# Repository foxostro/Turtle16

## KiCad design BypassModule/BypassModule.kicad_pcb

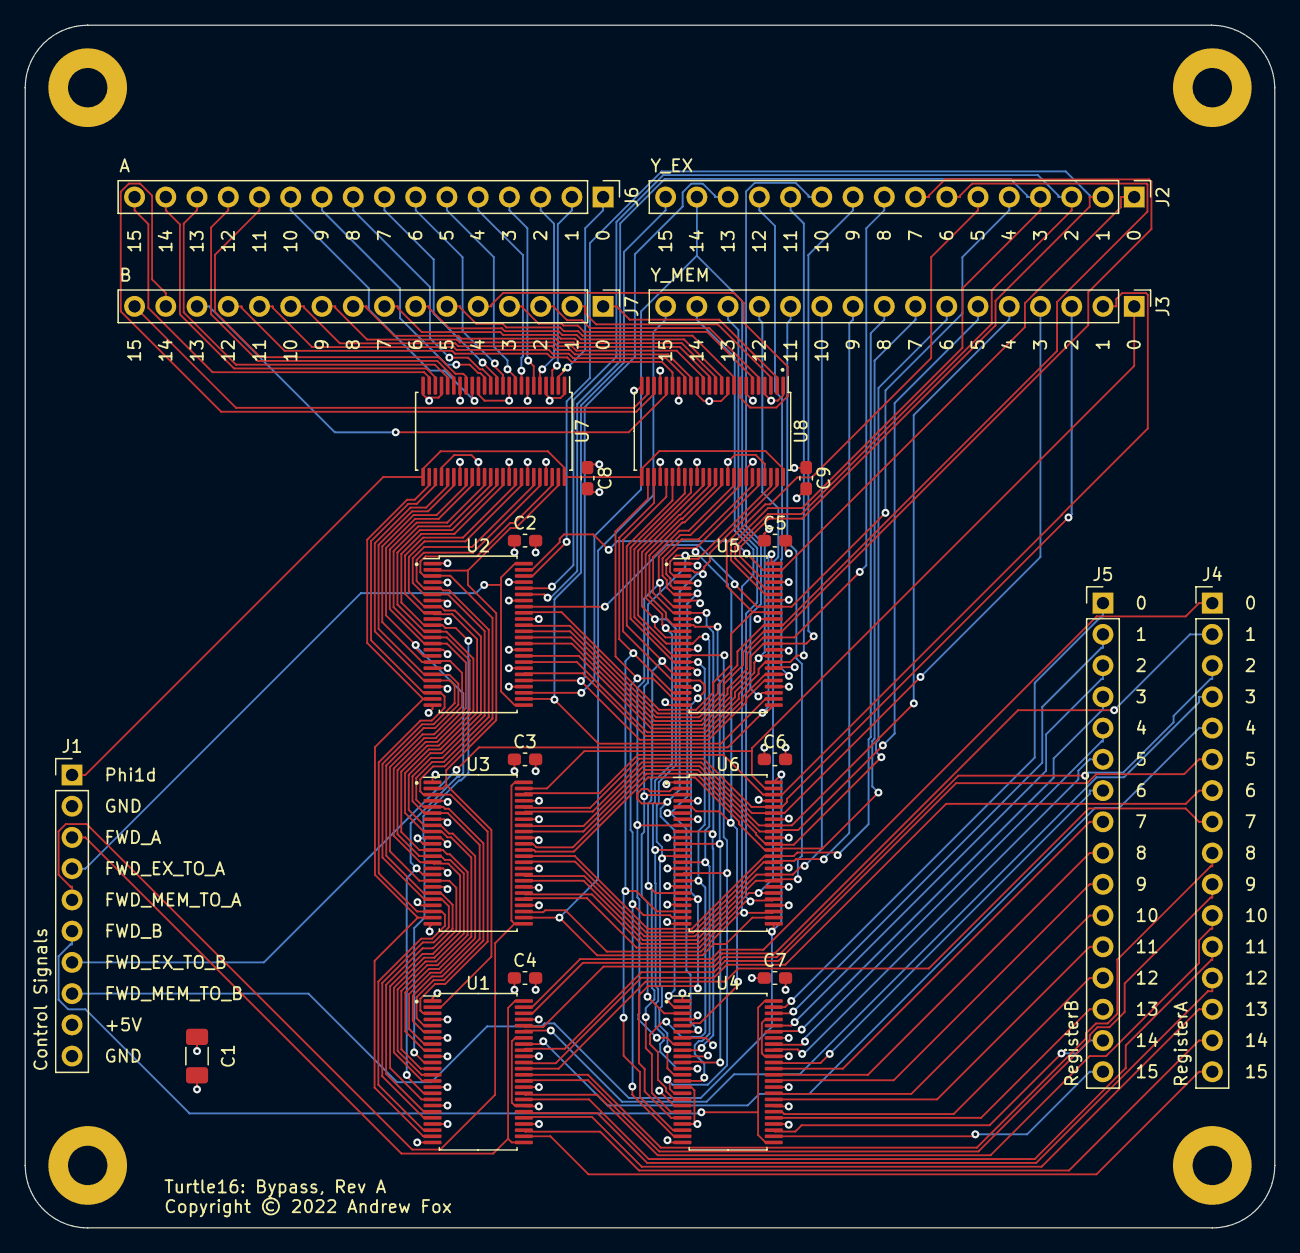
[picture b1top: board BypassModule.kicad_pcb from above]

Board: 4 copper layers, 101.6 x 97.8 mm, 28 parts (0 on the bottom side), 137 nets.

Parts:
C1: 100µF; C_1206_3216Metric_Pad1.33x1.80mm_HandSolder
C2, C3, C4, C5, C6, C7, C8, C9: 100nF; C_0603_1608Metric_Pad1.08x0.95mm_HandSolder
H1, H2, H3, H4: MountingHole_Pad; MountingHole_3.2mm_M3_Pad
J1: Control Signals; PinHeader_1x10_P2.54mm_Vertical
J2: Y_EX; PinHeader_1x16_P2.54mm_Vertical
J3: Y_MEM; PinHeader_1x16_P2.54mm_Vertical
J4: RegisterA; PinHeader_1x16_P2.54mm_Vertical
J5: RegisterB; PinHeader_1x16_P2.54mm_Vertical
J6: A; PinHeader_1x16_P2.54mm_Vertical
J7: B; PinHeader_1x16_P2.54mm_Vertical
U1, U2, U3, U4, U5, U6: 74AHCT16245; TSSOP-48_6.1x12.5mm_P0.5mm
U7, U8: 74ABT16374; TSSOP-48_6.1x12.5mm_P0.5mm

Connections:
/Bypass Prototype Inputs/FWD_A: J1.3, U1.25 (2~OE), U1.48 (1~OE)
/Bypass Prototype Inputs/FWD_B: J1.6, U4.25 (2~OE), U4.48 (1~OE)
/Bypass Prototype Inputs/FWD_EX_TO_A: J1.4, U2.25 (2~OE), U2.48 (1~OE)
/Bypass Prototype Inputs/FWD_EX_TO_B: J1.7, U5.25 (2~OE), U5.48 (1~OE)
/Bypass Prototype Inputs/FWD_MEM_TO_A: J1.5, U3.25 (2~OE), U3.48 (1~OE)
/Bypass Prototype Inputs/FWD_MEM_TO_B: J1.8, U6.25 (2~OE), U6.48 (1~OE)
/Bypass Prototype Inputs/Phi1d: J1.1, U7.25 (2CLK), U7.48 (1CLK), U8.25 (2CLK), U8.48 (1CLK)
/Bypass Prototype Inputs/RegisterA0: J4.1, U1.47 (1A1)
/Bypass Prototype Inputs/RegisterA1: J4.2, U1.46 (1A2)
/Bypass Prototype Inputs/RegisterA2: J4.3, U1.44 (1A3)
/Bypass Prototype Inputs/RegisterA3: J4.4, U1.43 (1A4)
/Bypass Prototype Inputs/RegisterA4: J4.5, U1.41 (1A5)
/Bypass Prototype Inputs/RegisterA5: J4.6, U1.40 (1A6)
/Bypass Prototype Inputs/RegisterA6: J4.7, U1.38 (1A7)
/Bypass Prototype Inputs/RegisterA7: J4.8, U1.37 (1A8)
/Bypass Prototype Inputs/RegisterA8: J4.9, U1.36 (2A1)
/Bypass Prototype Inputs/RegisterA9: J4.10, U1.35 (2A2)
/Bypass Prototype Inputs/RegisterA10: J4.11, U1.33 (2A3)
/Bypass Prototype Inputs/RegisterA11: J4.12, U1.32 (2A4)
/Bypass Prototype Inputs/RegisterA12: J4.13, U1.30 (2A5)
/Bypass Prototype Inputs/RegisterA13: J4.14, U1.29 (2A6)
/Bypass Prototype Inputs/RegisterA14: J4.15, U1.27 (2A7)
/Bypass Prototype Inputs/RegisterA15: J4.16, U1.26 (2A8)
/Bypass Prototype Inputs/RegisterB0: J5.1, U4.47 (1A1)
/Bypass Prototype Inputs/RegisterB1: J5.2, U4.46 (1A2)
/Bypass Prototype Inputs/RegisterB2: J5.3, U4.44 (1A3)
/Bypass Prototype Inputs/RegisterB3: J5.4, U4.43 (1A4)
/Bypass Prototype Inputs/RegisterB4: J5.5, U4.41 (1A5)
/Bypass Prototype Inputs/RegisterB5: J5.6, U4.40 (1A6)
/Bypass Prototype Inputs/RegisterB6: J5.7, U4.38 (1A7)
/Bypass Prototype Inputs/RegisterB7: J5.8, U4.37 (1A8)
/Bypass Prototype Inputs/RegisterB8: J5.9, U4.36 (2A1)
/Bypass Prototype Inputs/RegisterB9: J5.10, U4.35 (2A2)
/Bypass Prototype Inputs/RegisterB10: J5.11, U4.33 (2A3)
/Bypass Prototype Inputs/RegisterB11: J5.12, U4.32 (2A4)
/Bypass Prototype Inputs/RegisterB12: J5.13, U4.30 (2A5)
/Bypass Prototype Inputs/RegisterB13: J5.14, U4.29 (2A6)
/Bypass Prototype Inputs/RegisterB14: J5.15, U4.27 (2A7)
/Bypass Prototype Inputs/RegisterB15: J5.16, U4.26 (2A8)
/Bypass Prototype Inputs/Y_EX0: J2.1, U2.47 (1A1), U5.47 (1A1)
/Bypass Prototype Inputs/Y_EX1: J2.2, U2.46 (1A2), U5.46 (1A2)
/Bypass Prototype Inputs/Y_EX2: J2.3, U2.44 (1A3), U5.44 (1A3)
/Bypass Prototype Inputs/Y_EX3: J2.4, U2.43 (1A4), U5.43 (1A4)
/Bypass Prototype Inputs/Y_EX4: J2.5, U2.41 (1A5), U5.41 (1A5)
/Bypass Prototype Inputs/Y_EX5: J2.6, U2.40 (1A6), U5.40 (1A6)
/Bypass Prototype Inputs/Y_EX6: J2.7, U2.38 (1A7), U5.38 (1A7)
/Bypass Prototype Inputs/Y_EX7: J2.8, U2.37 (1A8), U5.37 (1A8)
/Bypass Prototype Inputs/Y_EX8: J2.9, U2.36 (2A1), U5.36 (2A1)
/Bypass Prototype Inputs/Y_EX9: J2.10, U2.35 (2A2), U5.35 (2A2)
/Bypass Prototype Inputs/Y_EX10: J2.11, U2.33 (2A3), U5.33 (2A3)
/Bypass Prototype Inputs/Y_EX11: J2.12, U2.32 (2A4), U5.32 (2A4)
/Bypass Prototype Inputs/Y_EX12: J2.13, U2.30 (2A5), U5.30 (2A5)
/Bypass Prototype Inputs/Y_EX13: J2.14, U2.29 (2A6), U5.29 (2A6)
/Bypass Prototype Inputs/Y_EX14: J2.15, U2.27 (2A7), U5.27 (2A7)
/Bypass Prototype Inputs/Y_EX15: J2.16, U2.26 (2A8), U5.26 (2A8)
/Bypass Prototype Inputs/Y_MEM0: J3.1, U3.47 (1A1), U6.47 (1A1)
/Bypass Prototype Inputs/Y_MEM1: J3.2, U3.46 (1A2), U6.46 (1A2)
/Bypass Prototype Inputs/Y_MEM2: J3.3, U3.44 (1A3), U6.44 (1A3)
/Bypass Prototype Inputs/Y_MEM3: J3.4, U3.43 (1A4), U6.43 (1A4)
/Bypass Prototype Inputs/Y_MEM4: J3.5, U3.41 (1A5), U6.41 (1A5)
/Bypass Prototype Inputs/Y_MEM5: J3.6, U3.40 (1A6), U6.40 (1A6)
/Bypass Prototype Inputs/Y_MEM6: J3.7, U3.38 (1A7), U6.38 (1A7)
/Bypass Prototype Inputs/Y_MEM7: J3.8, U3.37 (1A8), U6.37 (1A8)
/Bypass Prototype Inputs/Y_MEM8: J3.9, U3.36 (2A1), U6.36 (2A1)
/Bypass Prototype Inputs/Y_MEM9: J3.10, U3.35 (2A2), U6.35 (2A2)
/Bypass Prototype Inputs/Y_MEM10: J3.11, U3.33 (2A3), U6.33 (2A3)
/Bypass Prototype Inputs/Y_MEM11: J3.12, U3.32 (2A4), U6.32 (2A4)
/Bypass Prototype Inputs/Y_MEM12: J3.13, U3.30 (2A5), U6.30 (2A5)
/Bypass Prototype Inputs/Y_MEM13: J3.14, U3.29 (2A6), U6.29 (2A6)
/Bypass Prototype Inputs/Y_MEM14: J3.15, U3.27 (2A7), U6.27 (2A7)
/Bypass Prototype Inputs/Y_MEM15: J3.16, U3.26 (2A8), U6.26 (2A8)
/BypassPrototypeOutputs/A0: J6.1, U7.2 (1Q1)
/BypassPrototypeOutputs/A1: J6.2, U7.3 (1Q2)
/BypassPrototypeOutputs/A2: J6.3, U7.5 (1Q3)
/BypassPrototypeOutputs/A3: J6.4, U7.6 (1Q4)
/BypassPrototypeOutputs/A4: J6.5, U7.8 (1Q5)
/BypassPrototypeOutputs/A5: J6.6, U7.9 (1Q6)
/BypassPrototypeOutputs/A6: J6.7, U7.11 (1Q7)
/BypassPrototypeOutputs/A7: J6.8, U7.12 (1Q8)
/BypassPrototypeOutputs/A8: J6.9, U7.13 (2Q1)
/BypassPrototypeOutputs/A9: J6.10, U7.14 (2Q2)
/BypassPrototypeOutputs/A10: J6.11, U7.16 (2Q3)
/BypassPrototypeOutputs/A11: J6.12, U7.17 (2Q4)
/BypassPrototypeOutputs/A12: J6.13, U7.19 (2Q5)
/BypassPrototypeOutputs/A13: J6.14, U7.20 (2Q6)
/BypassPrototypeOutputs/A14: J6.15, U7.22 (2Q7)
/BypassPrototypeOutputs/A15: J6.16, U7.23 (2Q8)
/BypassPrototypeOutputs/B0: J7.1, U8.2 (1Q1)
/BypassPrototypeOutputs/B1: J7.2, U8.3 (1Q2)
/BypassPrototypeOutputs/B2: J7.3, U8.5 (1Q3)
/BypassPrototypeOutputs/B3: J7.4, U8.6 (1Q4)
/BypassPrototypeOutputs/B4: J7.5, U8.8 (1Q5)
/BypassPrototypeOutputs/B5: J7.6, U8.9 (1Q6)
/BypassPrototypeOutputs/B6: J7.7, U8.11 (1Q7)
/BypassPrototypeOutputs/B7: J7.8, U8.12 (1Q8)
/BypassPrototypeOutputs/B8: J7.9, U8.13 (2Q1)
/BypassPrototypeOutputs/B9: J7.10, U8.14 (2Q2)
/BypassPrototypeOutputs/B10: J7.11, U8.16 (2Q3)
/BypassPrototypeOutputs/B11: J7.12, U8.17 (2Q4)
/BypassPrototypeOutputs/B12: J7.13, U8.19 (2Q5)
/BypassPrototypeOutputs/B13: J7.14, U8.20 (2Q6)
/BypassPrototypeOutputs/B14: J7.15, U8.22 (2Q7)
/BypassPrototypeOutputs/B15: J7.16, U8.23 (2Q8)
/Operand Forwarding A/A_ID0: U1.2 (1B1), U2.2 (1B1), U3.2 (1B1), U7.47 (1D1)
/Operand Forwarding A/A_ID1: U1.3 (1B2), U2.3 (1B2), U3.3 (1B2), U7.46 (1D2)
/Operand Forwarding A/A_ID2: U1.5 (1B3), U2.5 (1B3), U3.5 (1B3), U7.44 (1D3)
/Operand Forwarding A/A_ID3: U1.6 (1B4), U2.6 (1B4), U3.6 (1B4), U7.43 (1D4)
/Operand Forwarding A/A_ID4: U1.8 (1B5), U2.8 (1B5), U3.8 (1B5), U7.41 (1D5)
/Operand Forwarding A/A_ID5: U1.9 (1B6), U2.9 (1B6), U3.9 (1B6), U7.40 (1D6)
/Operand Forwarding A/A_ID6: U1.11 (1B7), U2.11 (1B7), U3.11 (1B7), U7.38 (1D7)
/Operand Forwarding A/A_ID7: U1.12 (1B8), U2.12 (1B8), U3.12 (1B8), U7.37 (1D8)
/Operand Forwarding A/A_ID8: U1.13 (2B1), U2.13 (2B1), U3.13 (2B1), U7.36 (2D1)
/Operand Forwarding A/A_ID9: U1.14 (2B2), U2.14 (2B2), U3.14 (2B2), U7.35 (2D2)
/Operand Forwarding A/A_ID10: U1.16 (2B3), U2.16 (2B3), U3.16 (2B3), U7.33 (2D3)
/Operand Forwarding A/A_ID11: U1.17 (2B4), U2.17 (2B4), U3.17 (2B4), U7.32 (2D4)
/Operand Forwarding A/A_ID12: U1.19 (2B5), U2.19 (2B5), U3.19 (2B5), U7.30 (2D5)
/Operand Forwarding A/A_ID13: U1.20 (2B6), U2.20 (2B6), U3.20 (2B6), U7.29 (2D6)
/Operand Forwarding A/A_ID14: U1.22 (2B7), U2.22 (2B7), U3.22 (2B7), U7.27 (2D7)
/Operand Forwarding A/A_ID15: U1.23 (2B8), U2.23 (2B8), U3.23 (2B8), U7.26 (2D8)
/Operand Forwarding B/B_ID0: U4.2 (1B1), U5.2 (1B1), U6.2 (1B1), U8.47 (1D1)
/Operand Forwarding B/B_ID1: U4.3 (1B2), U5.3 (1B2), U6.3 (1B2), U8.46 (1D2)
/Operand Forwarding B/B_ID2: U4.5 (1B3), U5.5 (1B3), U6.5 (1B3), U8.44 (1D3)
/Operand Forwarding B/B_ID3: U4.6 (1B4), U5.6 (1B4), U6.6 (1B4), U8.43 (1D4)
/Operand Forwarding B/B_ID4: U4.8 (1B5), U5.8 (1B5), U6.8 (1B5), U8.41 (1D5)
/Operand Forwarding B/B_ID5: U4.9 (1B6), U5.9 (1B6), U6.9 (1B6), U8.40 (1D6)
/Operand Forwarding B/B_ID6: U4.11 (1B7), U5.11 (1B7), U6.11 (1B7), U8.38 (1D7)
/Operand Forwarding B/B_ID7: U4.12 (1B8), U5.12 (1B8), U6.12 (1B8), U8.37 (1D8)
/Operand Forwarding B/B_ID8: U4.13 (2B1), U5.13 (2B1), U6.13 (2B1), U8.36 (2D1)
/Operand Forwarding B/B_ID9: U4.14 (2B2), U5.14 (2B2), U6.14 (2B2), U8.35 (2D2)
/Operand Forwarding B/B_ID10: U4.16 (2B3), U5.16 (2B3), U6.16 (2B3), U8.33 (2D3)
/Operand Forwarding B/B_ID11: U4.17 (2B4), U5.17 (2B4), U6.17 (2B4), U8.32 (2D4)
/Operand Forwarding B/B_ID12: U4.19 (2B5), U5.19 (2B5), U6.19 (2B5), U8.30 (2D5)
/Operand Forwarding B/B_ID13: U4.20 (2B6), U5.20 (2B6), U6.20 (2B6), U8.29 (2D6)
/Operand Forwarding B/B_ID14: U4.22 (2B7), U5.22 (2B7), U6.22 (2B7), U8.27 (2D7)
/Operand Forwarding B/B_ID15: U4.23 (2B8), U5.23 (2B8), U6.23 (2B8), U8.26 (2D8)
GND: C1.2, C2.2, C3.2, C4.2, C5.2, C6.2, C7.2, C8.2, C9.2, H1.1, H2.1, H3.1, H4.1, J1.2, J1.10, U1.4 (GND), U1.10 (GND), U1.15 (GND), U1.21 (GND), U1.28 (GND), U1.34 (GND), U1.39 (GND), U1.45 (GND), U2.4 (GND), U2.10 (GND), U2.15 (GND), U2.21 (GND), U2.28 (GND), U2.34 (GND), U2.39 (GND), U2.45 (GND), U3.4 (GND), U3.10 (GND), U3.15 (GND), U3.21 (GND), U3.28 (GND), U3.34 (GND), U3.39 (GND), U3.45 (GND), U4.4 (GND), U4.10 (GND), U4.15 (GND), U4.21 (GND), U4.28 (GND), U4.34 (GND), U4.39 (GND), U4.45 (GND), U5.4 (GND), U5.10 (GND), U5.15 (GND), U5.21 (GND), U5.28 (GND), U5.34 (GND), U5.39 (GND), U5.45 (GND), U6.4 (GND), U6.10 (GND), U6.15 (GND), U6.21 (GND), U6.28 (GND), U6.34 (GND), U6.39 (GND), U6.45 (GND), U7.1 (1~OE), U7.4 (GND), U7.10 (GND), U7.15 (GND), U7.21 (GND), U7.24 (2~OE), U7.28 (GND), U7.34 (GND), U7.39 (GND), U7.45 (GND), U8.1 (1~OE), U8.4 (GND), U8.10 (GND), U8.15 (GND), U8.21 (GND), U8.24 (2~OE), U8.28 (GND), U8.34 (GND), U8.39 (GND), U8.45 (GND)
VCC: C1.1, C2.1, C3.1, C4.1, C5.1, C6.1, C7.1, C8.1, C9.1, J1.9, U1.1 (1DIR), U1.7 (VCC), U1.18 (VCC), U1.24 (2DIR), U1.31 (VCC), U1.42 (VCC), U2.1 (1DIR), U2.7 (VCC), U2.18 (VCC), U2.24 (2DIR), U2.31 (VCC), U2.42 (VCC), U3.1 (1DIR), U3.7 (VCC), U3.18 (VCC), U3.24 (2DIR), U3.31 (VCC), U3.42 (VCC), U4.1 (1DIR), U4.7 (VCC), U4.18 (VCC), U4.24 (2DIR), U4.31 (VCC), U4.42 (VCC), U5.1 (1DIR), U5.7 (VCC), U5.18 (VCC), U5.24 (2DIR), U5.31 (VCC), U5.42 (VCC), U6.1 (1DIR), U6.7 (VCC), U6.18 (VCC), U6.24 (2DIR), U6.31 (VCC), U6.42 (VCC), U7.7 (VCC), U7.18 (VCC), U7.31 (VCC), U7.42 (VCC), U8.7 (VCC), U8.18 (VCC), U8.31 (VCC), U8.42 (VCC)

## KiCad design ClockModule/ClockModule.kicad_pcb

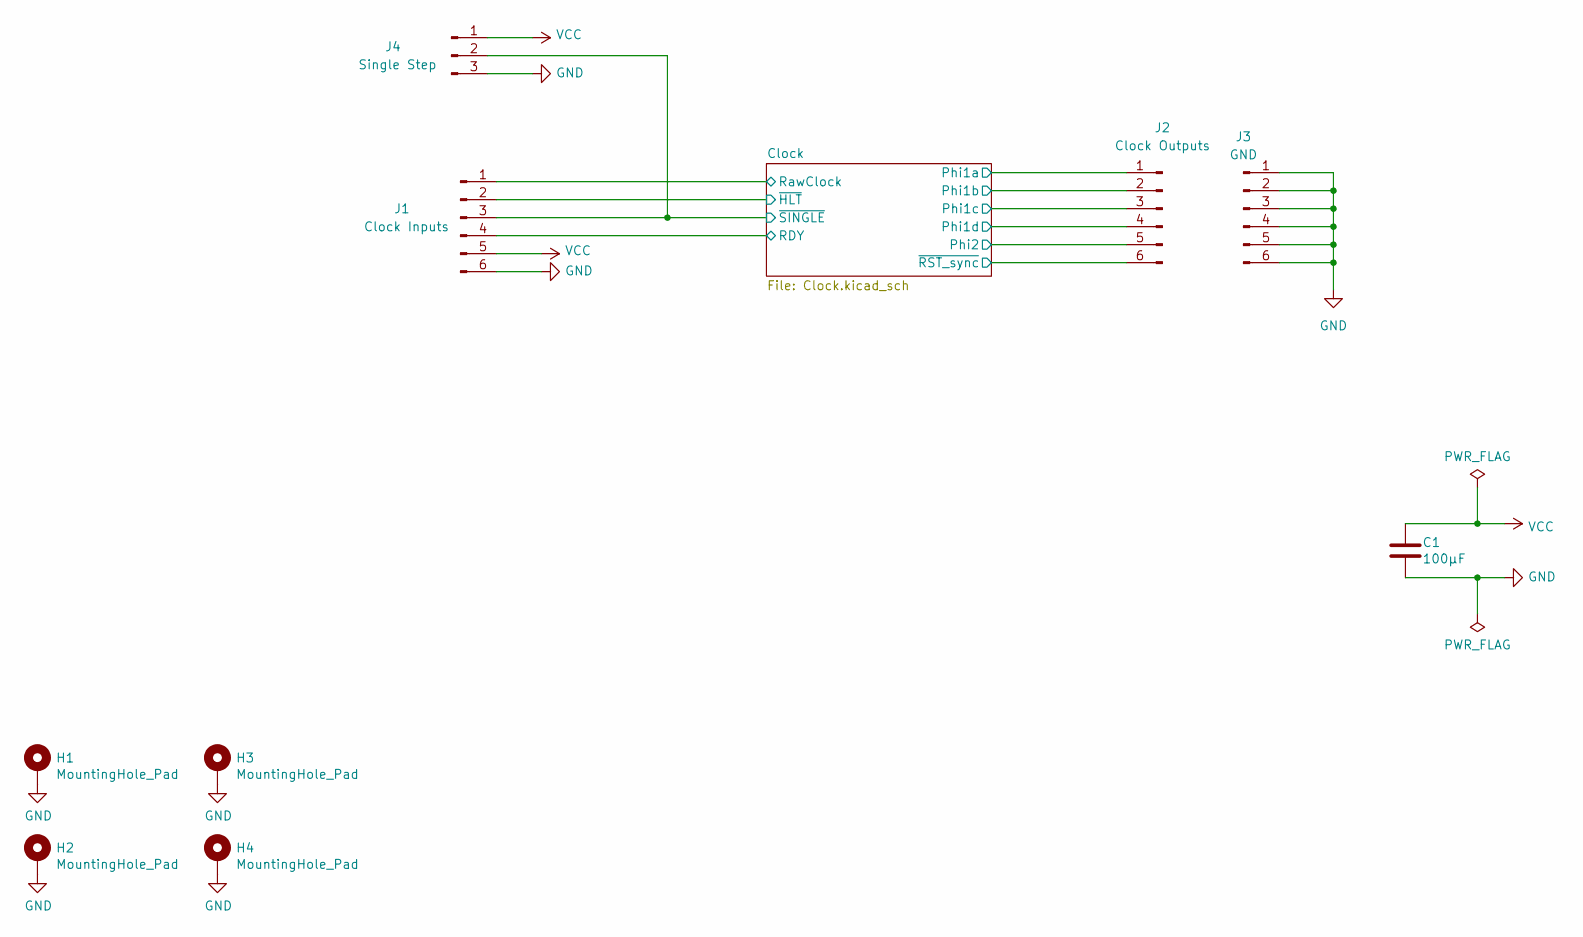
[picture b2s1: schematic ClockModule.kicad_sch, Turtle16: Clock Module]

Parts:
C1: 100µF; C_1206_3216Metric_Pad1.33x1.80mm_HandSolder
H1, H2, H3, H4: MountingHole_Pad; MountingHole_3.2mm_M3_Pad
J1: Clock Inputs; PinHeader_1x06_P2.54mm_Vertical
J2: Clock Outputs; PinHeader_1x06_P2.54mm_Vertical
J3: GND; PinHeader_1x06_P2.54mm_Vertical
J4: Single Step; PinHeader_1x03_P2.54mm_Vertical

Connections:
/Clock/Phi1a: J2.1; also elsewhere on the board
/Clock/Phi1b: J2.2; also elsewhere on the board
/Clock/Phi1c: J2.3; also elsewhere on the board
/Clock/Phi1d: J2.4; also elsewhere on the board
/Clock/Phi2: J2.5; also elsewhere on the board
/Clock/RDY: J1.4; also elsewhere on the board
/Clock/RawClock: J1.1; also elsewhere on the board
/Clock/~HLT: J1.2; also elsewhere on the board
/Clock/~RST_sync: J2.6; also elsewhere on the board
/Clock/~SINGLE: J1.3, J4.2; also elsewhere on the board
GND: C1.2, H1.1, H2.1, H3.1, H4.1, J1.6, J3.1, J3.2, J3.3, J3.4, J3.5, J3.6, J4.3; also elsewhere on the board
VCC: C1.1, J1.5, J4.1; also elsewhere on the board

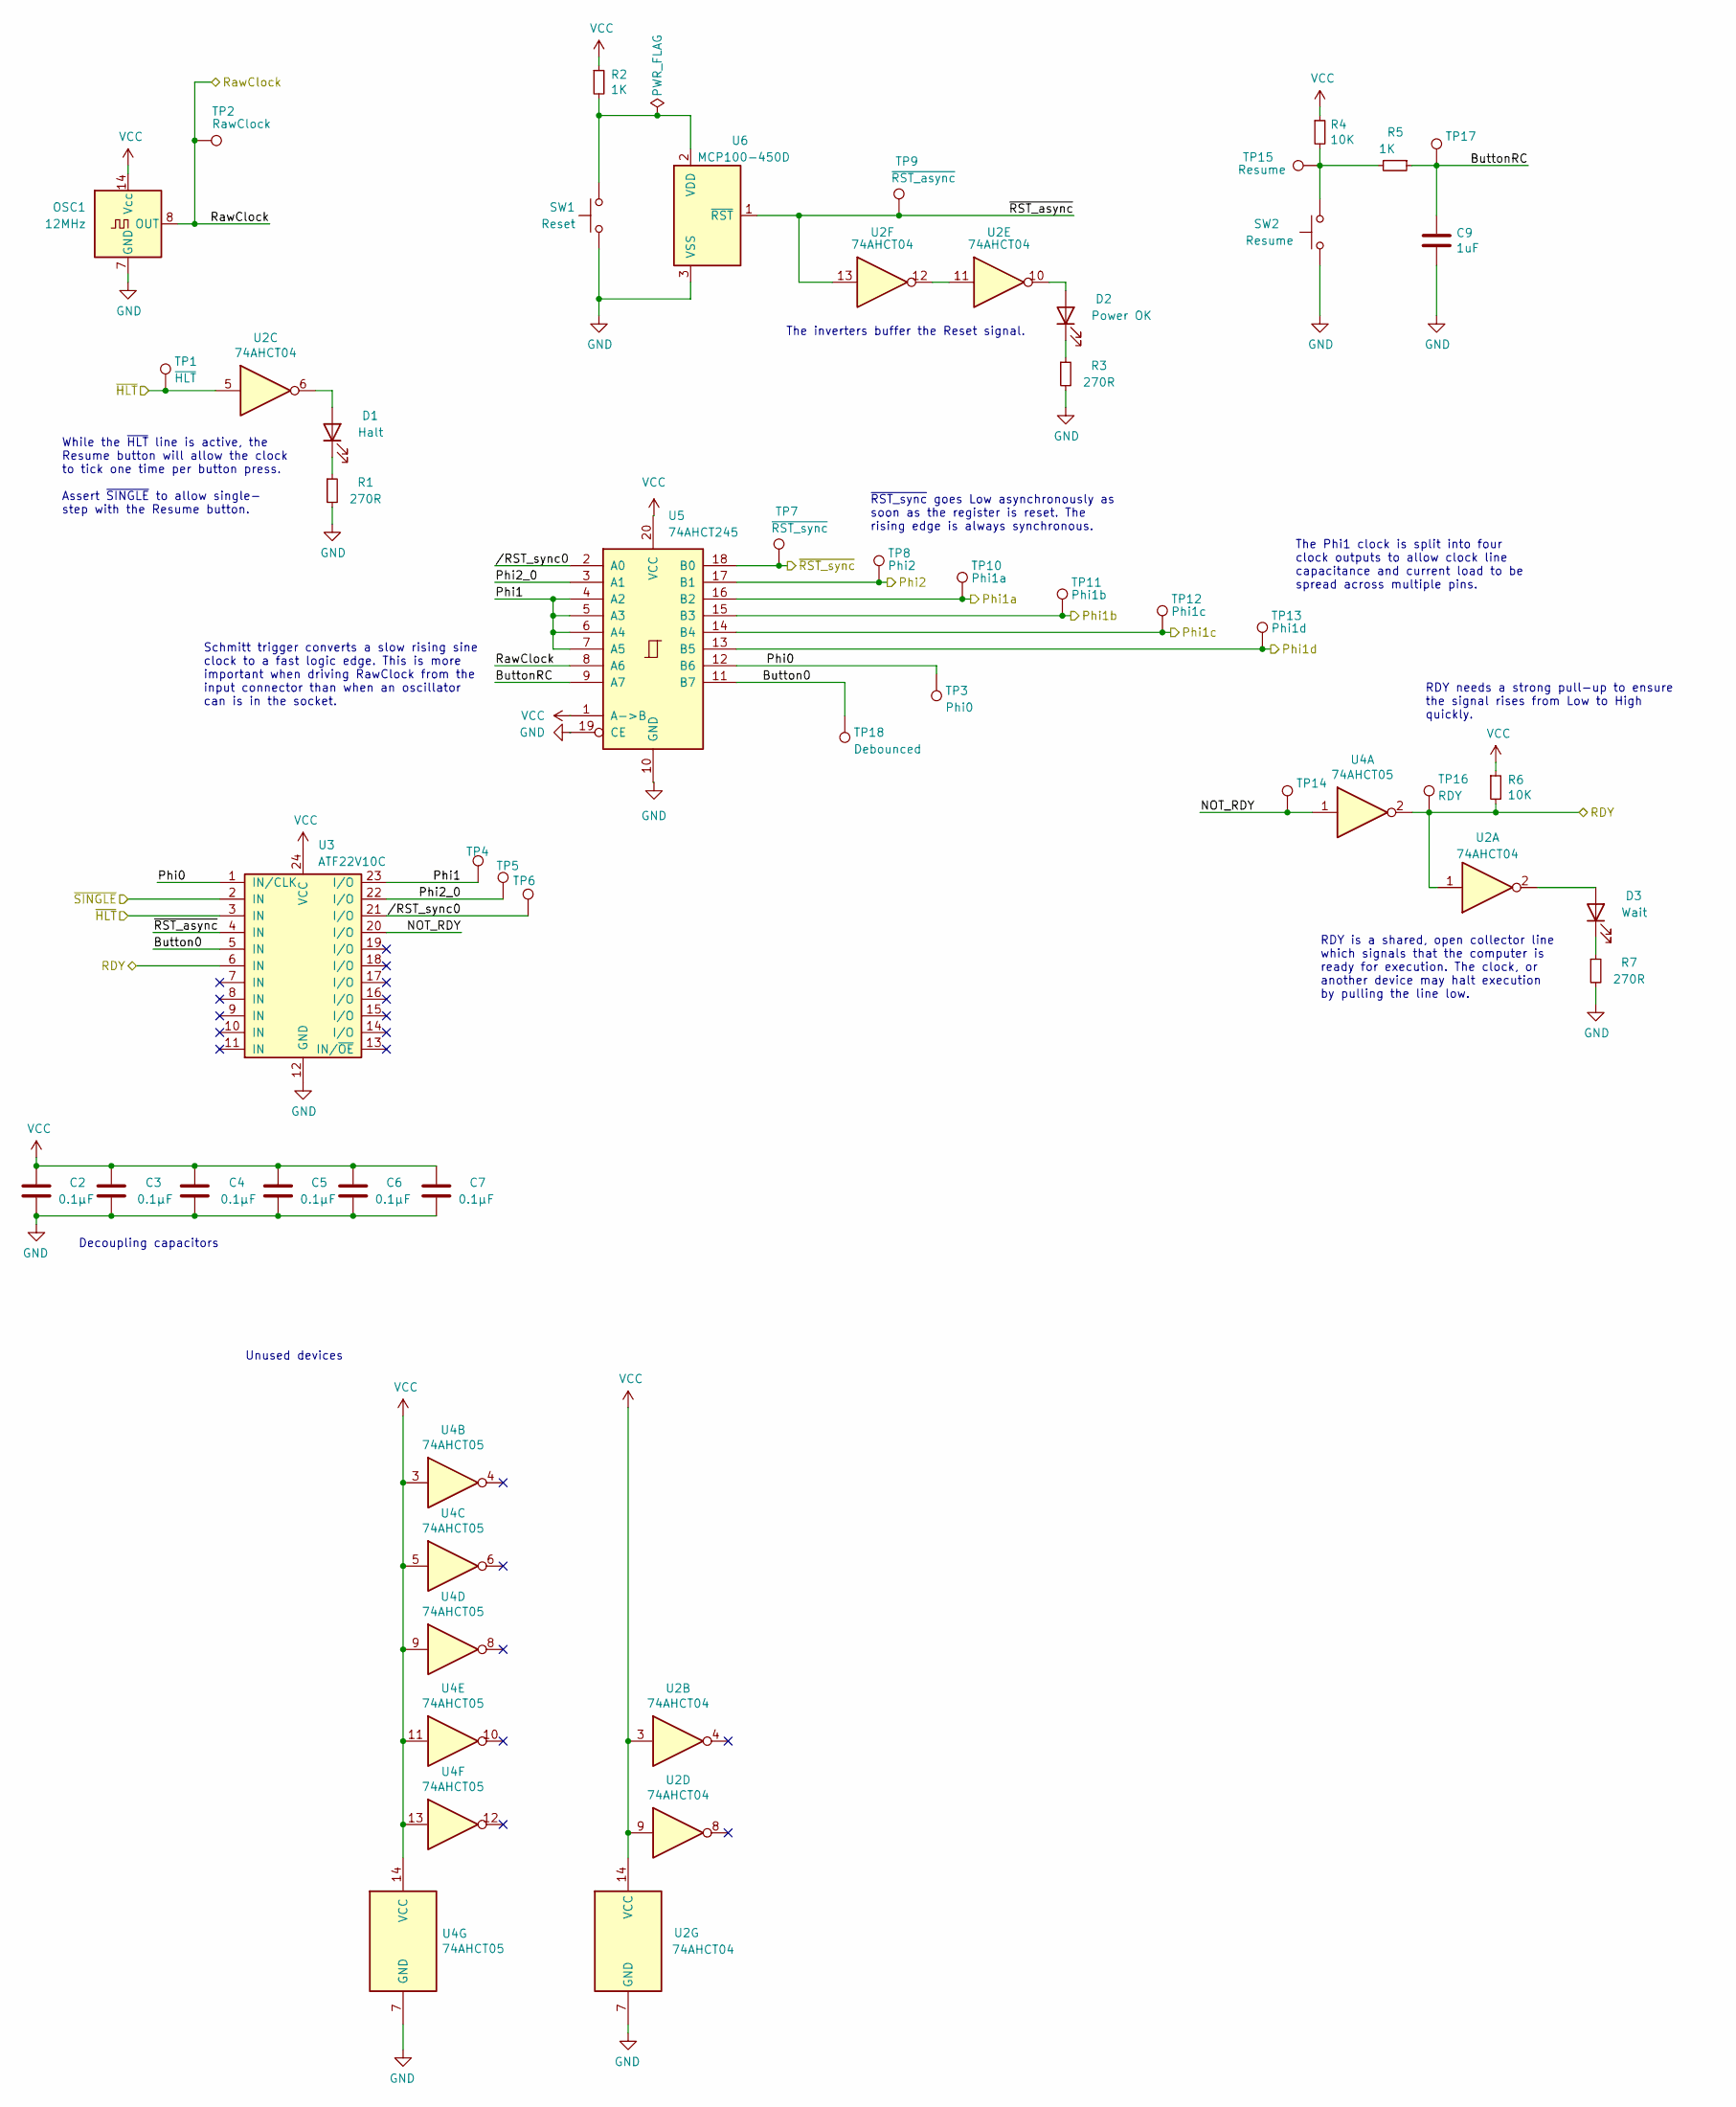
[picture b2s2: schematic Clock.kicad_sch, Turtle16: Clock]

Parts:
C2, C3, C4, C5, C6, C7: 0.1µF; C_0603_1608Metric_Pad1.08x0.95mm_HandSolder
C9: 1uF; C_0603_1608Metric_Pad1.08x0.95mm_HandSolder
D1: Halt; LED_0805_2012Metric
D2: Power OK; LED_0805_2012Metric
D3: Wait; LED_0805_2012Metric
OSC1: 12MHz; Oscillator_DIP-14
R1, R3, R7: 270R; C_0603_1608Metric
R2, R5: 1K; R_0603_1608Metric_Pad0.98x0.95mm_HandSolder
R4, R6: 10K; R_0603_1608Metric_Pad0.98x0.95mm_HandSolder
SW1: Reset; SW_PUSH_6mm_H5mm
SW2: Resume; SW_PUSH_6mm_H5mm
TP1: ~{HLT}; TestPoint_Pad_D1.0mm
TP2: RawClock; TestPoint_Pad_D1.0mm
TP3: Phi0; TestPoint_Pad_D1.0mm
TP4: TestPoint_Pad_D1.0mm
TP5, TP6, TP14, TP17: TP; TestPoint_Pad_D1.0mm
TP7: ~{RST_sync}; TestPoint_Pad_D1.0mm
TP8: Phi2; TestPoint_Pad_D1.0mm
TP9: ~{RST_async}; TestPoint_Pad_D1.0mm
TP10: Phi1a; TestPoint_Pad_D1.0mm
TP11: Phi1b; TestPoint_Pad_D1.0mm
TP12: Phi1c; TestPoint_Pad_D1.0mm
TP13: Phi1d; TestPoint_Pad_D1.0mm
TP15: Resume; TestPoint_Pad_D1.0mm
TP16: RDY; TestPoint_Pad_D1.0mm
TP18: Debounced; TestPoint_Pad_D1.0mm
U2: 74AHCT04; TSSOP-14_4.4x5mm_P0.65mm
U3: ATF22V10C; DIP-24_W7.62mm_Socket
U4: 74AHCT05; TSSOP-14_4.4x5mm_P0.65mm
U5: 74AHCT245; TSSOP-20_4.4x6.5mm_P0.65mm
U6: MCP100-450D; TO-92

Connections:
/Clock/Button0: TP18.1, U3.5 (IN), U5.11 (B7)
/Clock/ButtonRC: C9.1, R5.1, TP17.1, U5.9 (A7)
/Clock/NOT_RDY: TP14.1, U3.20 (I/O), U4.1
/Clock/Phi0: TP3.1, U3.1 (IN/CLK), U5.12 (B6)
/Clock/Phi1: TP4.1, U3.23 (I/O), U5.4 (A2), U5.5 (A3), U5.6 (A4), U5.7 (A5)
/Clock/Phi1a: TP10.1, U5.16 (B2); also elsewhere on the board
/Clock/Phi1b: TP11.1, U5.15 (B3); also elsewhere on the board
/Clock/Phi1c: TP12.1, U5.14 (B4); also elsewhere on the board
/Clock/Phi1d: TP13.1, U5.13 (B5); also elsewhere on the board
/Clock/Phi2: TP8.1, U5.17 (B1); also elsewhere on the board
/Clock/Phi2_0: TP5.1, U3.22 (I/O), U5.3 (A1)
/Clock/RDY: R6.2, TP16.1, U2.1, U3.6 (IN), U4.2; also elsewhere on the board
/Clock/RawClock: OSC1.8 (OUT), TP2.1, U5.8 (A6); also elsewhere on the board
/Clock//RST_sync0: TP6.1, U3.21 (I/O), U5.2 (A0)
/Clock/~HLT: TP1.1, U2.5, U3.3 (IN); also elsewhere on the board
/Clock/~RST_async: TP9.1, U2.13, U3.4 (IN), U6.1 (~RST)
/Clock/~RST_sync: TP7.1, U5.18 (B0); also elsewhere on the board
/Clock/~SINGLE: U3.2 (IN); also elsewhere on the board
GND: C2.2, C3.2, C4.2, C5.2, C6.2, C7.2, C9.2, OSC1.7 (GND), R1.2, R3.2, R7.2, SW1.1, SW2.1, U2.7 (GND), U3.12 (GND), U4.7 (GND), U5.10 (GND), U5.19 (CE), U6.3 (VSS); also elsewhere on the board
unnamed: D1.2 (A), U2.6
unnamed: D1.1 (K), R1.1
unnamed: D2.2 (A), U2.10
unnamed: D2.1 (K), R3.1
unnamed: D3.2 (A), U2.2
unnamed: D3.1 (K), R7.1
unnamed: R4.2, R5.2, SW2.2, TP15.1
unnamed: U2.11, U2.12
unnamed: R2.2, SW1.2, U6.2 (VDD)
VCC: C2.1, C3.1, C4.1, C5.1, C6.1, C7.1, OSC1.14 (Vcc), R2.1, R4.1, R6.1, U2.3, U2.9, U2.14 (VCC), U3.24 (VCC), U4.3, U4.5, U4.9, U4.11, U4.13, U4.14 (VCC), U5.1 (A->B), U5.20 (VCC); also elsewhere on the board

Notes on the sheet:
~{RST_sync} goes Low asynchronously as soon as the register is reset. The rising edge is always synchronous.
RDY is a shared, open collector line which signals that the computer is ready for execution. The clock, or another device may halt execution by pulling the line low.
The inverters buffer the Reset signal.
RDY needs a strong pull-up to ensure the signal rises from Low to High quickly.
The Phi1 clock is split into four clock outputs to allow clock line capacitance and current load to be spread across multiple pins.
Schmitt trigger converts a slow rising sine clock to a fast logic edge. This is more important when driving RawClock from the input connector than when an oscillator can is in the socket.
Unused devices
While the ~{HLT} line is active, the Resume button will allow the clock to tick one time per button press. Assert ~{SINGLE} to allow single- step with the Resume button.
Decoupling capacitors

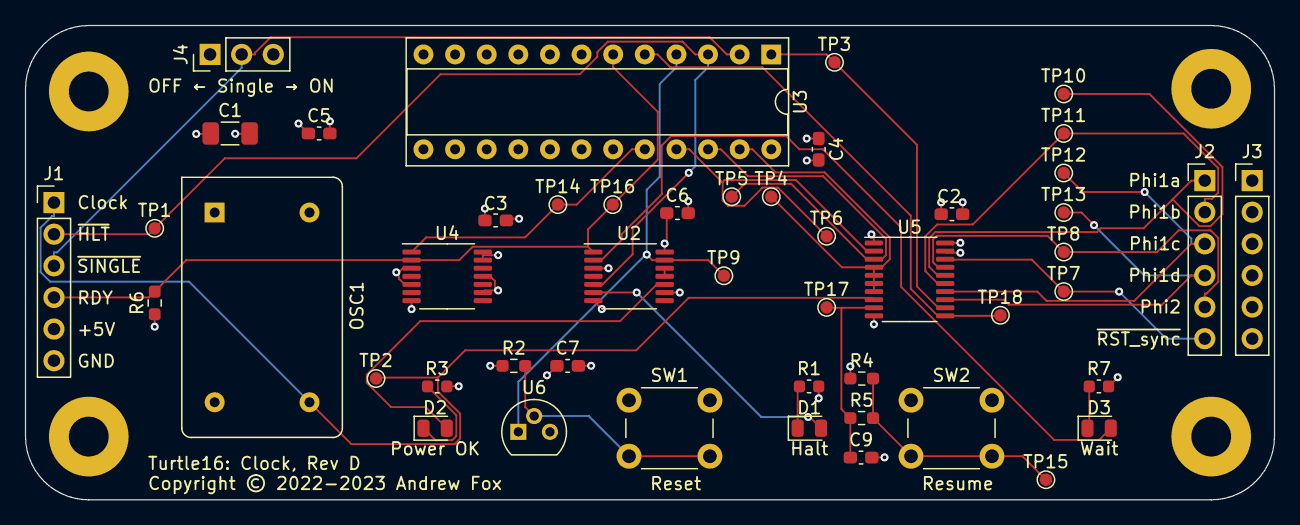
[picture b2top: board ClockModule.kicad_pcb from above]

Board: 4 copper layers, 100.3 x 38.1 mm, 52 parts (0 on the bottom side), 29 nets.

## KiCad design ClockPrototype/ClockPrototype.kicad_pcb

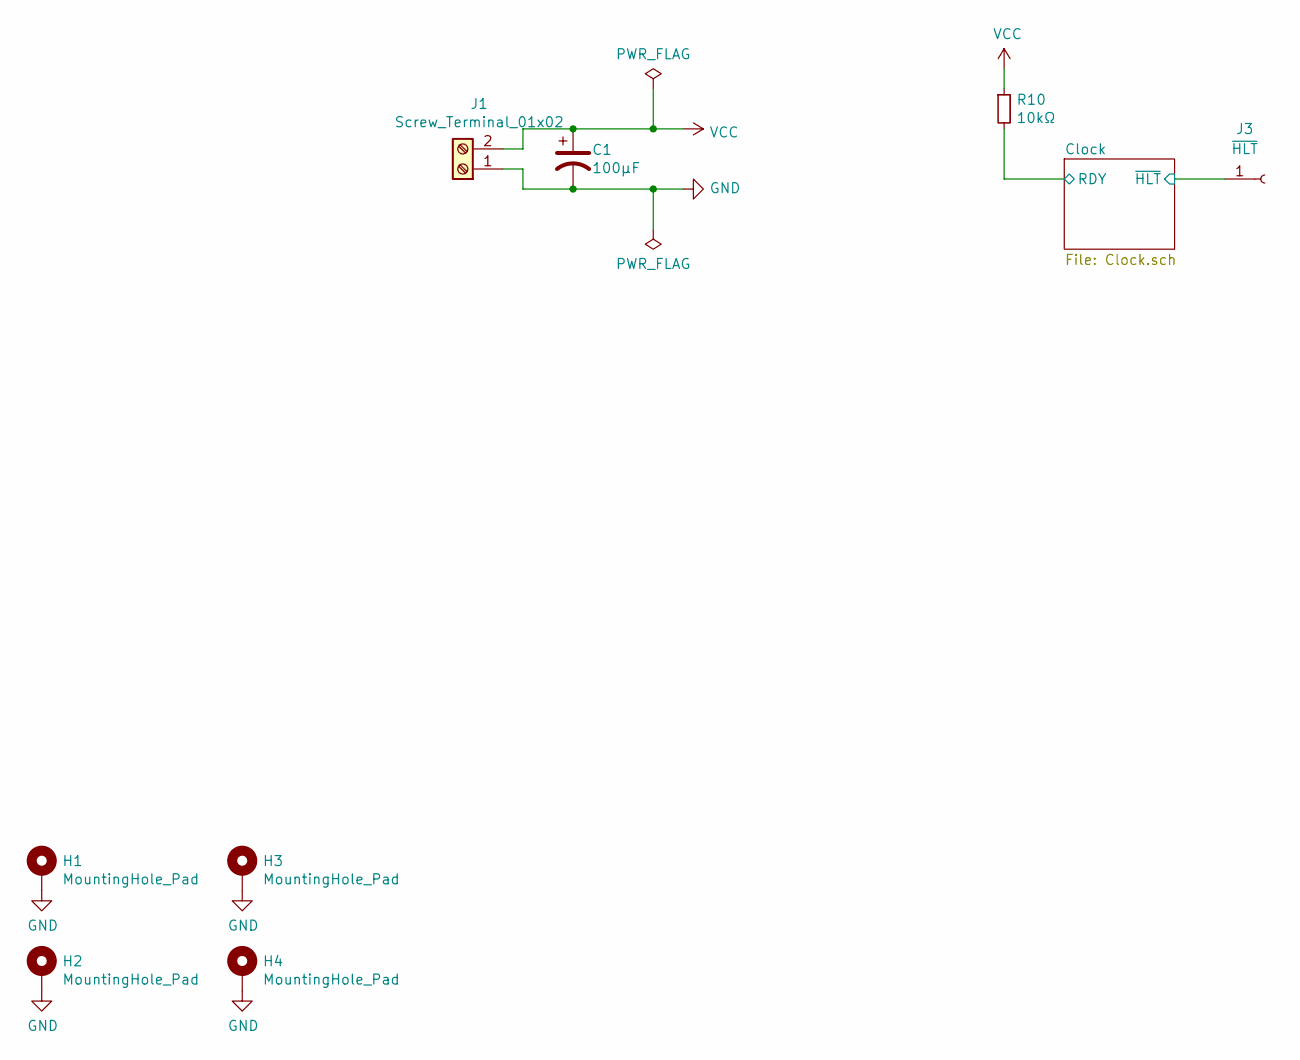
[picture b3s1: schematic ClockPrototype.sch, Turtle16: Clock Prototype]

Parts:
C1: 100µF; C_1206_3216Metric_Pad1.33x1.80mm_HandSolder
H1, H2, H3, H4: MountingHole_Pad; MountingHole_3.2mm_M3_Pad
J1: Screw_Terminal_01x02; TerminalBlock_MetzConnect_Type055_RT01502HDWU_1x02_P5.00mm_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
J3: ~HLT; PinSocket_1x01_P2.54mm_Vertical
R10: 10kΩ; R_0603_1608Metric_Pad0.98x0.95mm_HandSolder

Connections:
/Clock/RDY: R10.2; also elsewhere on the board
/Clock/~HLT: J3.1; also elsewhere on the board
GND: C1.2, H1.1, H2.1, H3.1, H4.1, J1.1; also elsewhere on the board
VCC: C1.1, J1.2, R10.1; also elsewhere on the board

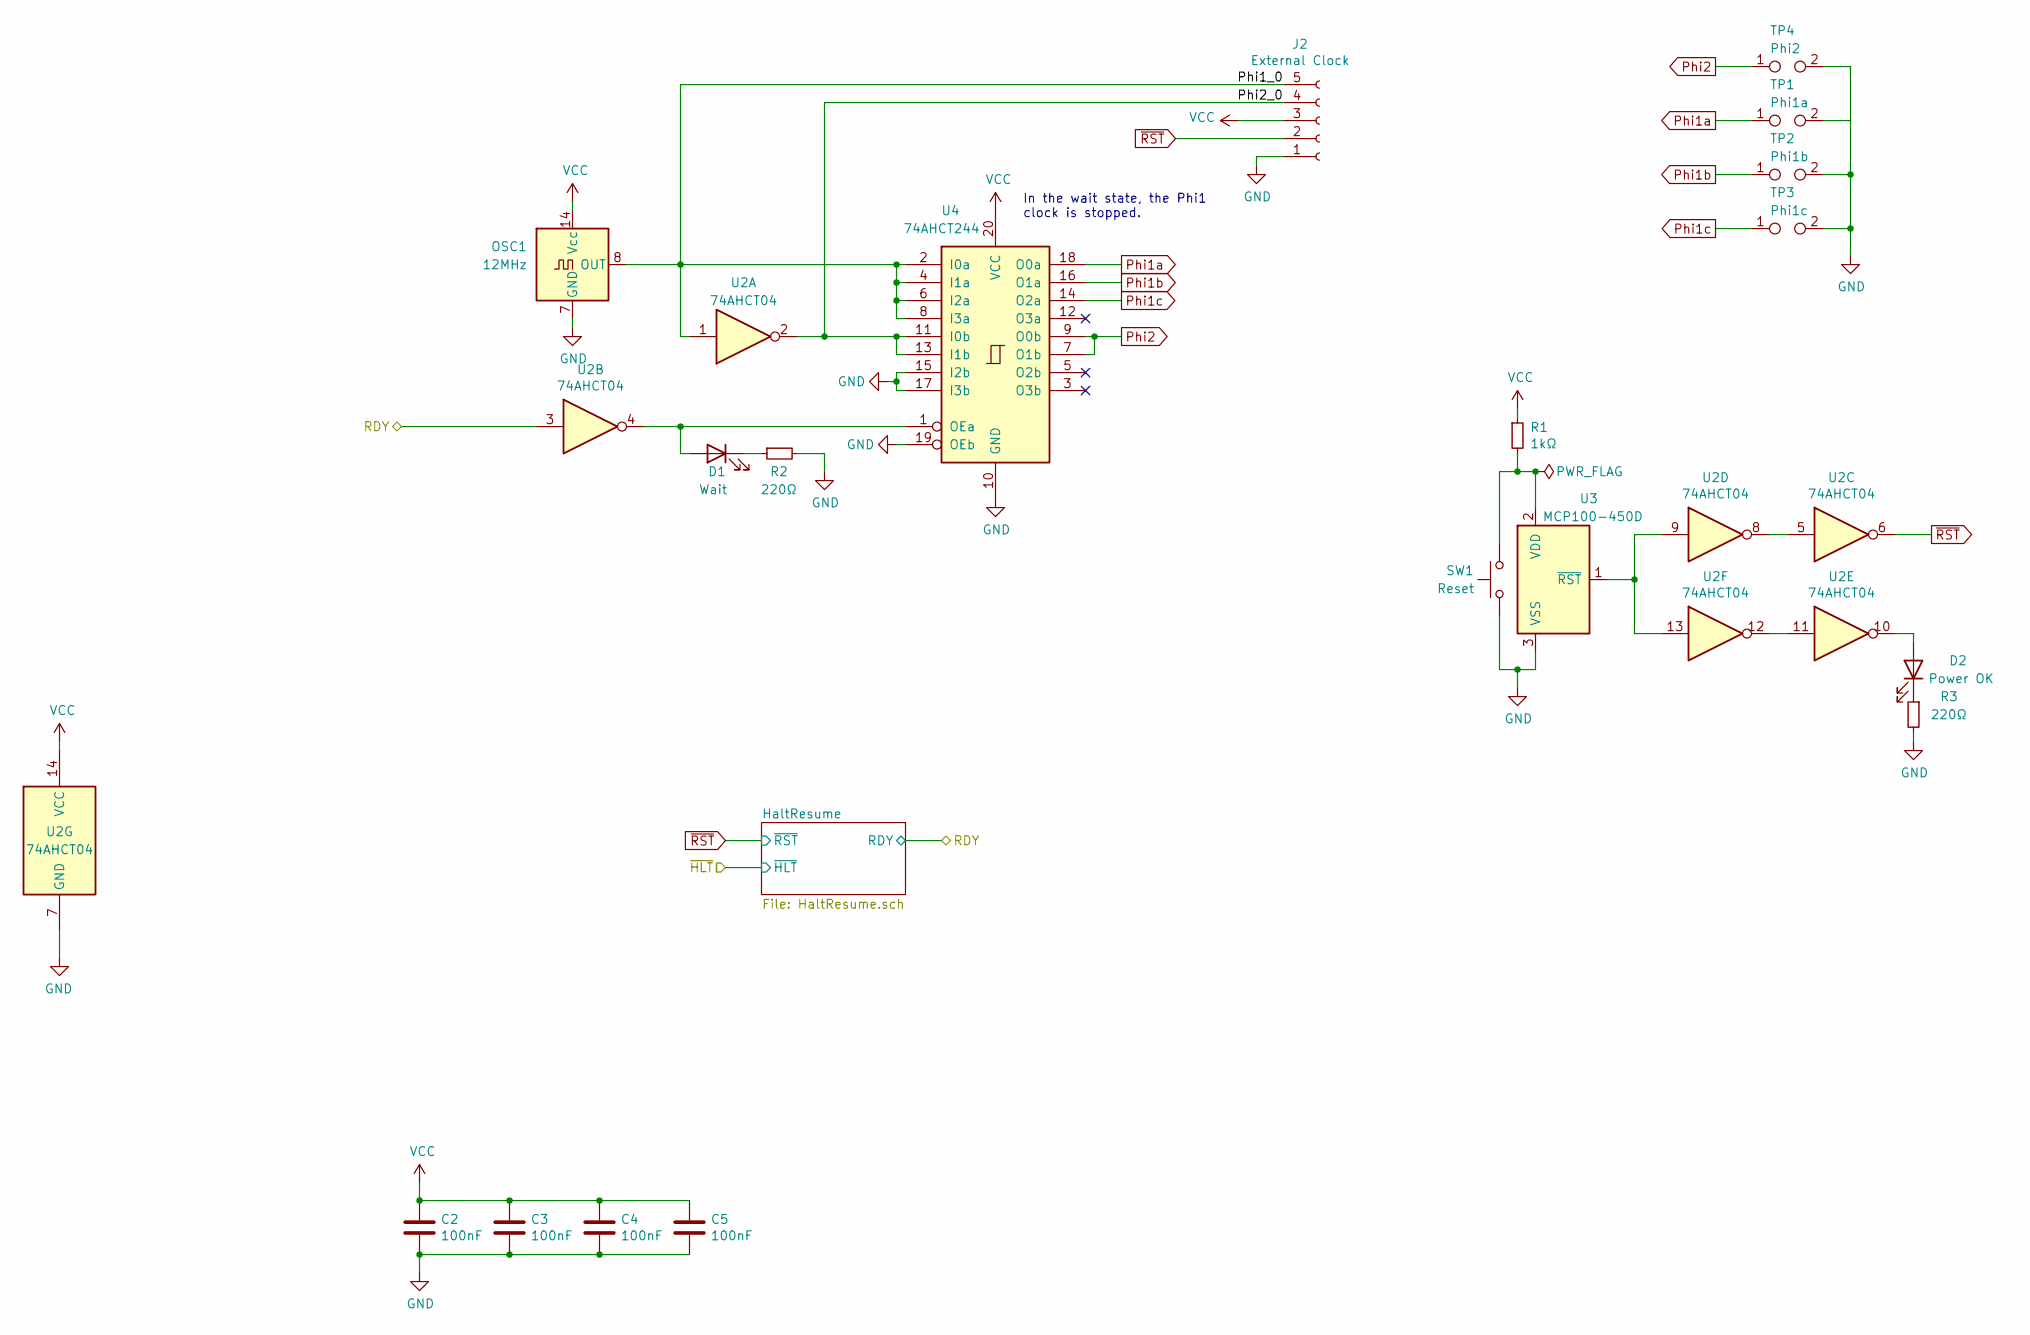
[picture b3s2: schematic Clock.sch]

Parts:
C2, C3, C4, C5: 100nF; C_0603_1608Metric_Pad1.08x0.95mm_HandSolder
D1: Wait; LED_D5.0mm
D2: Power OK; LED_D5.0mm
J2: External Clock; PinSocket_1x05_P2.54mm_Vertical
OSC1: 12MHz; Oscillator_DIP-14
R1: 1kΩ; R_0603_1608Metric_Pad0.98x0.95mm_HandSolder
R2, R3: 220Ω; R_0603_1608Metric_Pad0.98x0.95mm_HandSolder
SW1: Reset; SW_PUSH_6mm_H5mm
TP1: Phi1a; TestPoint_2Pads_Pitch5.08mm_Drill1.3mm
TP2: Phi1b; TestPoint_2Pads_Pitch5.08mm_Drill1.3mm
TP3: Phi1c; TestPoint_2Pads_Pitch5.08mm_Drill1.3mm
TP4: Phi2; TestPoint_2Pads_Pitch5.08mm_Drill1.3mm
U2: 74AHCT04; TSSOP-14_4.4x5mm_P0.65mm
U3: MCP100-450D; TO-92
U4: 74AHCT244; TSSOP-20_4.4x6.5mm_P0.65mm

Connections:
/Clock/Phi1_0: J2.5, OSC1.8 (OUT), U2.1, U4.2 (I0a), U4.4 (I1a), U4.6 (I2a), U4.8 (I3a)
/Clock/Phi2_0: J2.4, U2.2, U4.11 (I0b), U4.13 (I1b)
/Clock/RDY: U2.3; also elsewhere on the board
GND: C2.2, C3.2, C4.2, C5.2, J2.1, OSC1.7 (GND), R2.2, R3.2, SW1.1, TP1.2, TP2.2, TP3.2, TP4.2, U2.7 (GND), U3.3 (VSS), U4.10 (GND), U4.15 (I2b), U4.17 (I3b), U4.19 (OEb); also elsewhere on the board
unnamed: D1.1 (K), R2.1
unnamed: D1.2 (A), U2.4, U4.1 (OEa)
unnamed: D2.1 (K), R3.1
unnamed: D2.2 (A), U2.10
unnamed: R1.2, SW1.2, U3.2 (VDD)
unnamed: U2.5, U2.8
unnamed: U2.11, U2.12
unnamed: U2.9, U2.13, U3.1 (~RST)
Phi1a: TP1.1, U4.18 (O0a)
Phi1b: TP2.1, U4.16 (O1a)
Phi1c: TP3.1, U4.14 (O2a)
Phi2: TP4.1, U4.7 (O1b), U4.9 (O0b)
VCC: C2.1, C3.1, C4.1, C5.1, J2.3, OSC1.14 (Vcc), R1.1, U2.14 (VCC), U4.20 (VCC); also elsewhere on the board
~RST: J2.2, U2.6; also elsewhere on the board

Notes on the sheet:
In the wait state, the Phi1 clock is stopped.

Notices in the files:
BypassModule/BypassModule.kicad_pcb:
Copyright © 2022 Andrew Fox
ClockModule/ClockModule.kicad_pcb:
Copyright © 2022-2023 Andrew Fox
ClockPrototype/ClockPrototype.kicad_pcb:
Copyright © 2021 Andrew Fox
ControlModuleTestFixture/ControlModuleTestFixture.kicad_pcb:
Copyright © 2023
